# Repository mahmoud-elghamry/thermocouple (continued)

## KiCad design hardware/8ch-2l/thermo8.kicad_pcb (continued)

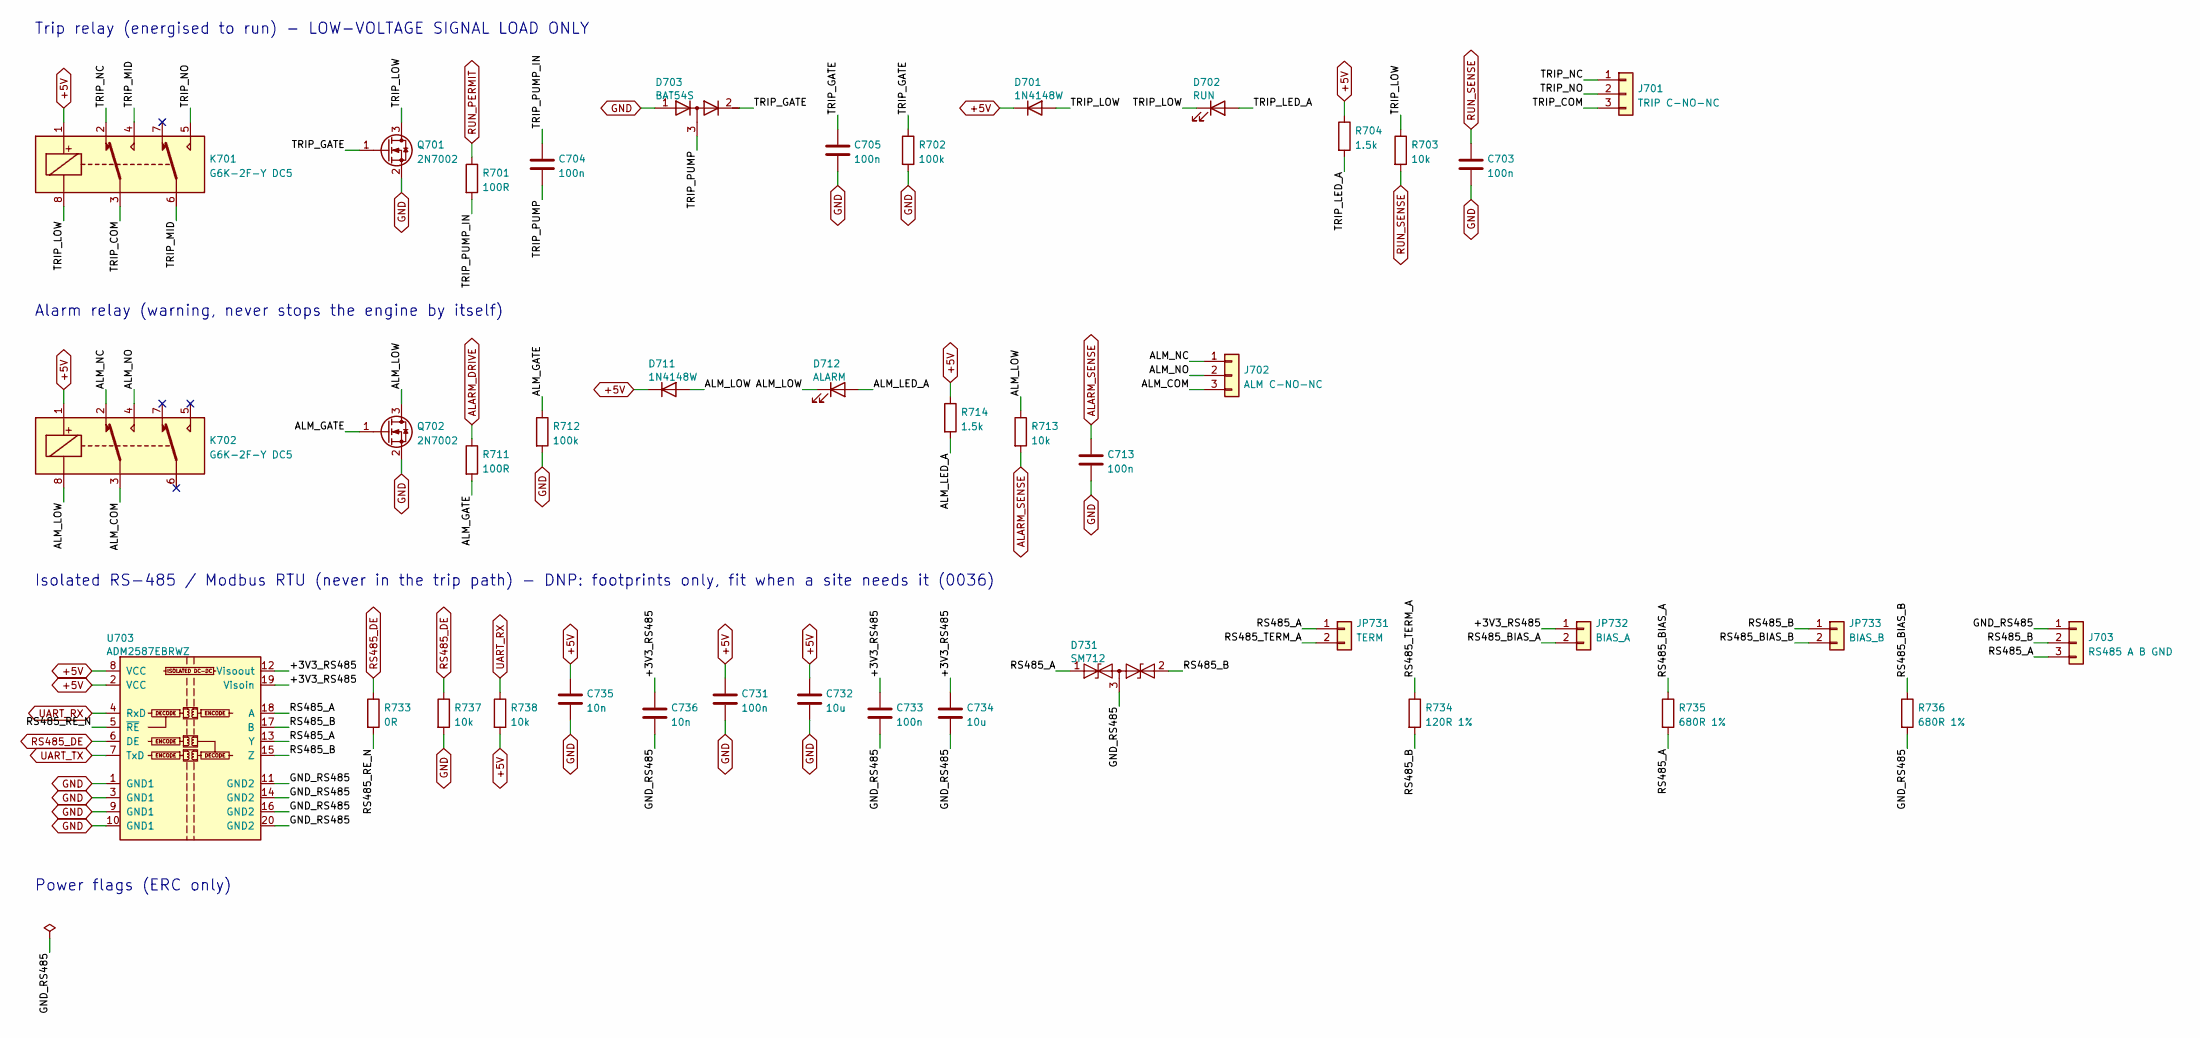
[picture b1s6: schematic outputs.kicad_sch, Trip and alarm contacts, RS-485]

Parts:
C703, C704, C705, C713, C731, C733: 100n; C_0805_2012Metric; MPN CC0805KRX7R9BB104; LCSC C49678
C732, C734: 10u; C_0805_2012Metric; MPN CL21B106KOQNNNE; LCSC C95841
C735, C736: 10n; C_0805_2012Metric; MPN CL21B103KBANNNC; LCSC C1710
D701, D711: 1N4148W; D_SOD-123; MPN 1N4148W-7-F; LCSC C83528
D702: RUN; LED_D3.0mm; MPN 3A4GUD; LCSC C52034646
D703: BAT54S; SOT-23; MPN BAT54S,215; LCSC C47546
D712: ALARM; LED_D3.0mm; MPN 204-10SURD/S530-A3-L; LCSC C99771
D731: SM712; SOT-23; MPN SM712.TCT; LCSC C12067
J701: TRIP C-NO-NC; TerminalBlock_Phoenix_MKDS-1,5-3_1x03_P5.00mm_Horizontal; MPN WJ128V-5.0-3P; LCSC C8270
J702: ALM C-NO-NC; TerminalBlock_Phoenix_MKDS-1,5-3_1x03_P5.00mm_Horizontal; MPN WJ128V-5.0-3P; LCSC C8270
J703: RS485 A B GND; TerminalBlock_Phoenix_MKDS-1,5-3_1x03_P5.00mm_Horizontal; MPN WJ128V-5.0-3P; LCSC C8270
JP731: TERM; PinHeader_1x02_P2.54mm_Vertical; MPN PZ254V-11-02P; LCSC C492401
JP732: BIAS_A; PinHeader_1x02_P2.54mm_Vertical; MPN PZ254V-11-02P; LCSC C492401
JP733: BIAS_B; PinHeader_1x02_P2.54mm_Vertical; MPN PZ254V-11-02P; LCSC C492401
K701, K702: G6K-2F-Y DC5; Relay_DPDT_Omron_G6K-2F-Y; MPN G6K-2F-Y DC5; LCSC C2982926
Q701, Q702: 2N7002; SOT-23; MPN 2N7002; LCSC C8545
R701, R711: 100R; R_0805_2012Metric; MPN 0805W8F1000T5E; LCSC C17408
R702, R712: 100k; R_0805_2012Metric; MPN 0805W8F1003T5E; LCSC C149504
R703, R713, R737, R738: 10k; R_0805_2012Metric; MPN 0805W8F1002T5E; LCSC C17414
R704, R714: 1.5k; R_0805_2012Metric; MPN 0805W8F1501T5E; LCSC C4310
R733: 0R; R_0805_2012Metric; MPN 0805W8F0000T5E; LCSC C17477
R734: 120R 1%; R_0805_2012Metric; MPN 0805W8F1200T5E; LCSC C17437
R735, R736: 680R 1%; R_0805_2012Metric; MPN 0805W8F6800T5E; LCSC C17798
U703: ADM2587EBRWZ; SOIC-20W_7.5x12.8mm_P1.27mm; MPN ADM2587EBRWZ-REEL7; LCSC C12081

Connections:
+5V: C731.1, C732.1, C735.1, D701.1 (K), D711.1 (K), K701.1, K702.1, R704.1, R714.1, R738.2, U703.2 (VCC), U703.8 (VCC); also elsewhere on the board
/OUTPUTS/+3V3_RS485: C733.1, C734.1, C736.1, JP732.1, U703.12 (Visoout), U703.19 (Visoin)
/OUTPUTS/ALM_COM: J702.3, K702.3
/OUTPUTS/ALM_GATE: Q702.1 (G), R711.2, R712.1
/OUTPUTS/ALM_LED_A: D712.2 (A), R714.2
/OUTPUTS/ALM_LOW: D711.2 (A), D712.1 (K), K702.8, Q702.3 (D), R713.1
/OUTPUTS/ALM_NC: J702.1, K702.2
/OUTPUTS/ALM_NO: J702.2, K702.4
/OUTPUTS/GND_RS485: C733.2, C734.2, C736.2, D731.3 (common), J703.1, R736.2, U703.11 (GND2), U703.14 (GND2), U703.16 (GND2), U703.20 (GND2)
/OUTPUTS/RS485_A: D731.1 (A1), J703.3, JP731.1, R735.2, U703.13 (Y), U703.18 (A)
/OUTPUTS/RS485_B: D731.2 (A2), J703.2, JP733.1, R734.2, U703.15 (Z), U703.17 (B)
/OUTPUTS/RS485_BIAS_A: JP732.2, R735.1
/OUTPUTS/RS485_BIAS_B: JP733.2, R736.1
/OUTPUTS/RS485_RE_N: R733.2, U703.5 (~RE)
/OUTPUTS/RS485_TERM_A: JP731.2, R734.1
/OUTPUTS/TRIP_COM: J701.3, K701.3
/OUTPUTS/TRIP_GATE: C705.1, D703.2 (K), Q701.1 (G), R702.1
/OUTPUTS/TRIP_LED_A: D702.2 (A), R704.2
/OUTPUTS/TRIP_LOW: D701.2 (A), D702.1 (K), K701.8, Q701.3 (D), R703.1
/OUTPUTS/TRIP_MID: K701.4, K701.6
/OUTPUTS/TRIP_NC: J701.1, K701.2
/OUTPUTS/TRIP_NO: J701.2, K701.5
/OUTPUTS/TRIP_PUMP: C704.2, D703.3 (common)
/OUTPUTS/TRIP_PUMP_IN: C704.1, R701.2
ALARM_DRIVE: R711.1; also elsewhere on the board
ALARM_SENSE: C713.1, R713.2; also elsewhere on the board
GND: C703.2, C705.2, C713.2, C731.2, C732.2, C735.2, D703.1 (A), Q701.2 (S), Q702.2 (S), R702.2, R712.2, R737.2, U703.1 (GND1), U703.3 (GND1), U703.9 (GND1), U703.10 (GND1); also elsewhere on the board
RS485_DE: R733.1, R737.1, U703.6 (DE); also elsewhere on the board
RUN_PERMIT: R701.1; also elsewhere on the board
RUN_SENSE: C703.1, R703.2; also elsewhere on the board
UART_RX: R738.1, U703.4 (RxD); also elsewhere on the board
UART_TX: U703.7 (TxD); also elsewhere on the board

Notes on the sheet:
Trip relay (energised to run) - LOW-VOLTAGE SIGNAL LOAD ONLY
Alarm relay (warning, never stops the engine by itself)
Isolated RS-485 / Modbus RTU (never in the trip path) - DNP: footprints only, fit when a site needs it (0036)
Power flags (ERC only)

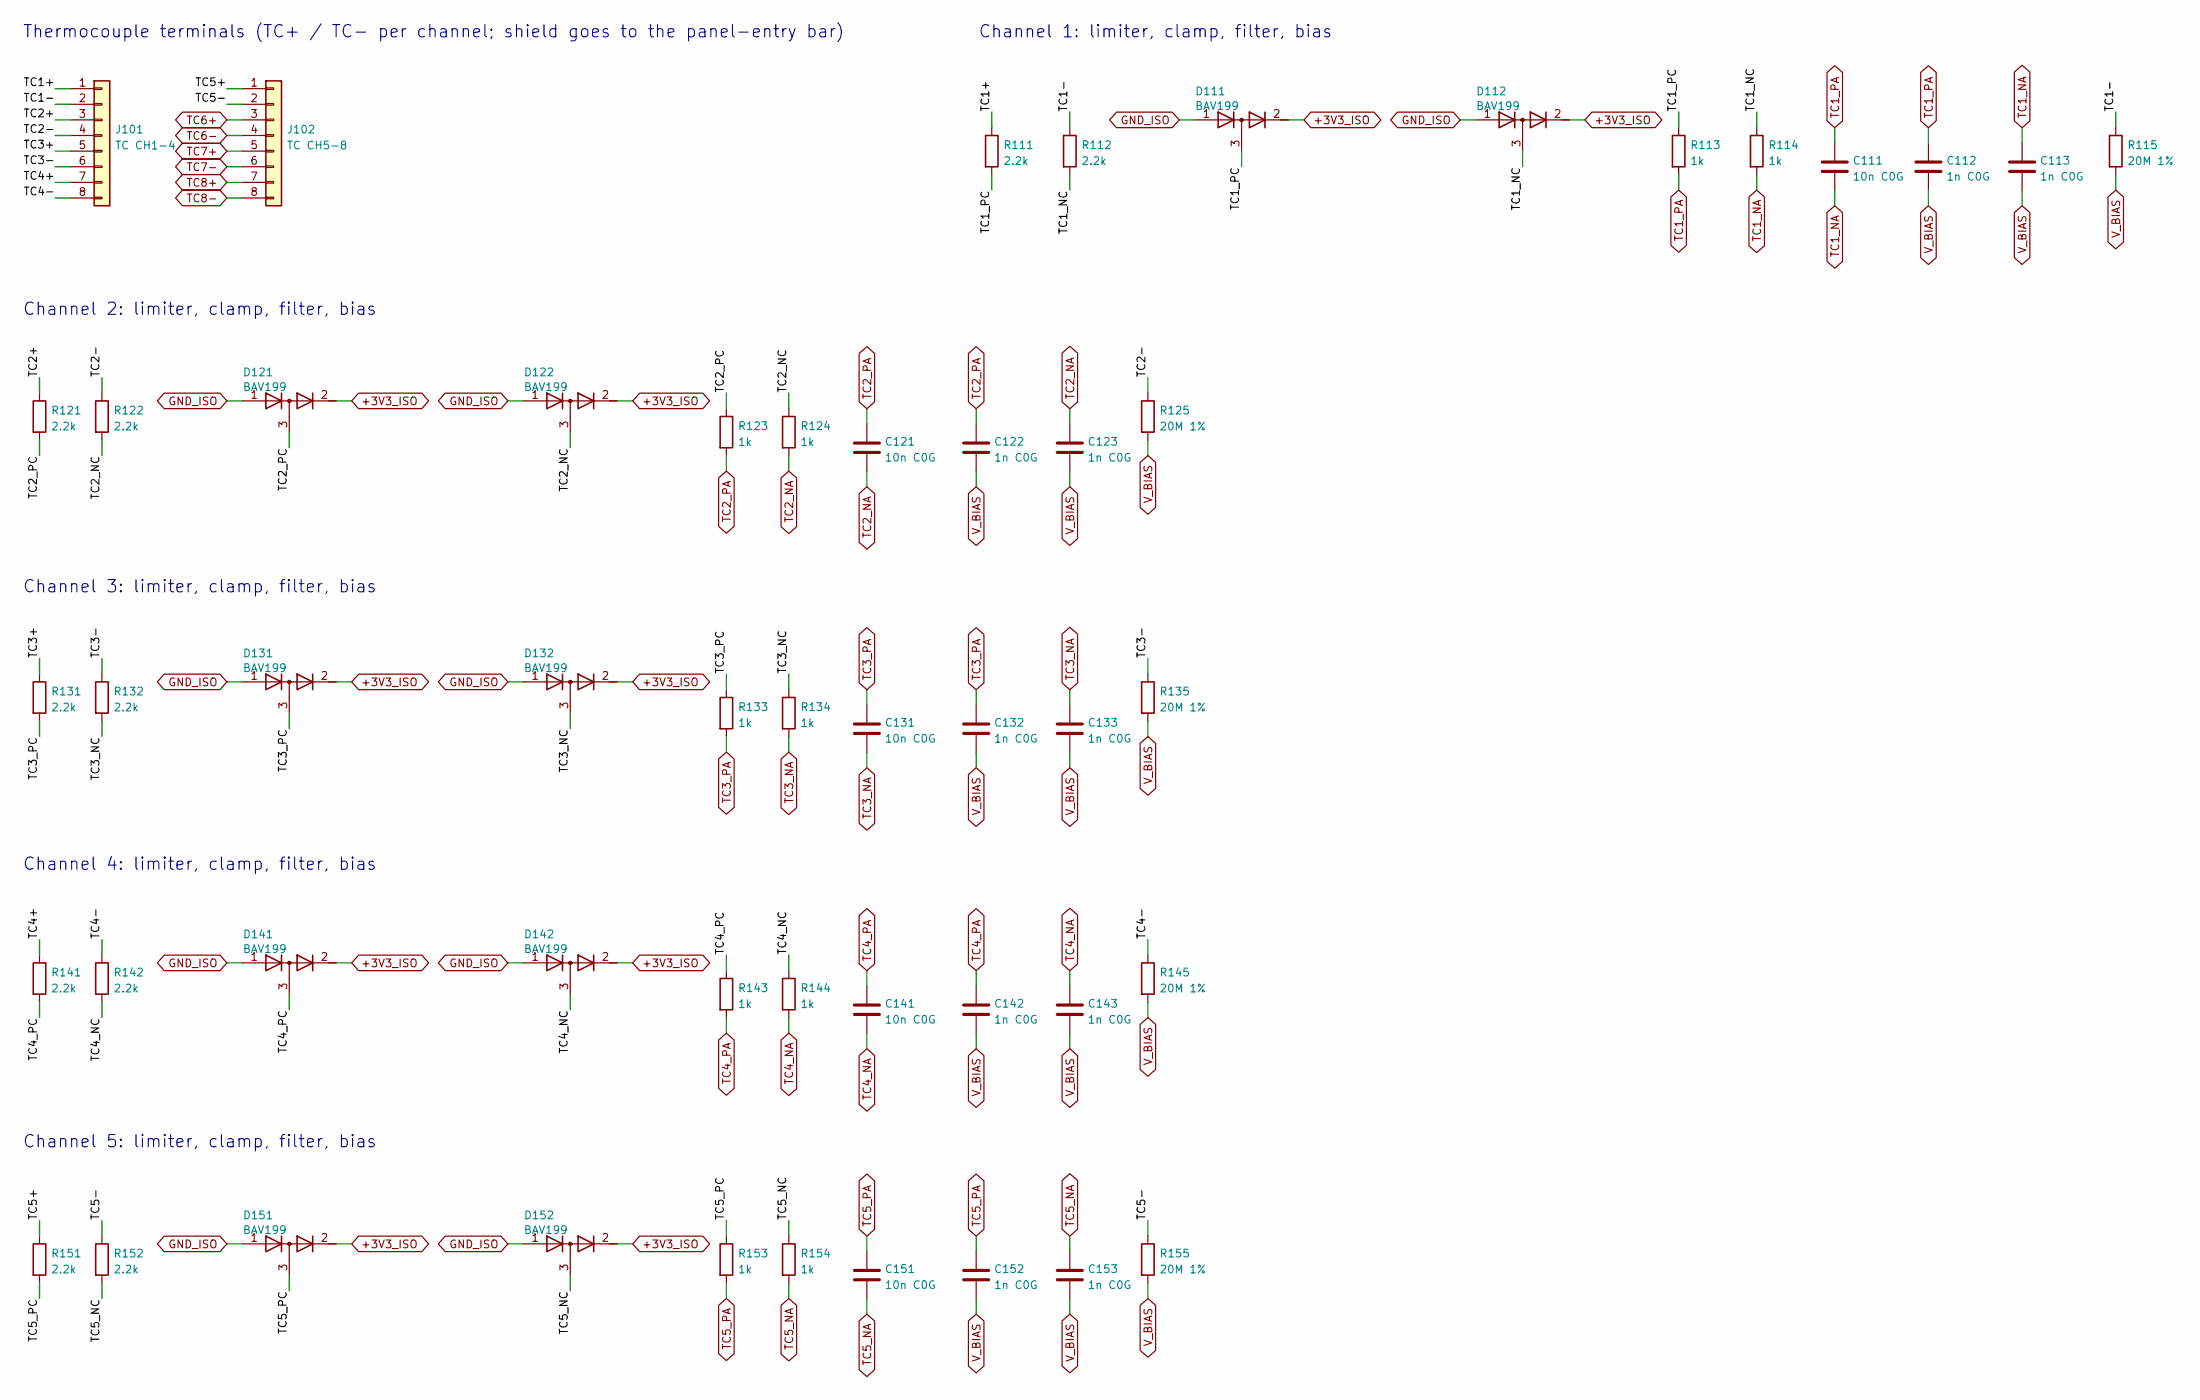
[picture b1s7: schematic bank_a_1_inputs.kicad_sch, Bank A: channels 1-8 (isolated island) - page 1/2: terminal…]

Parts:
C111, C121, C131, C141, C151: 10n C0G; C_0805_2012Metric; MPN GRM2195C1H103JA01D; LCSC C97905
C112, C113, C122, C123, C132, C133, C142, C143, C152, C153: 1n C0G; C_0805_2012Metric; MPN CL21C102JBCNNNC; LCSC C1791
D111, D112, D121, D122, D131, D132, D141, D142, D151, D152: BAV199; SOT-23; MPN BAV199,215; LCSC C40919
J101: TC CH1-4; PhoenixContact_MC_1,5_8-G-3.81_1x08_P3.81mm_Horizontal; MPN WJ15EDGRC-3.81-8P; LCSC C14235
J102: TC CH5-8; PhoenixContact_MC_1,5_8-G-3.81_1x08_P3.81mm_Horizontal; MPN WJ15EDGRC-3.81-8P; LCSC C14235
R111, R112, R121, R122, R131, R132, R141, R142, R151, R152: 2.2k; R_0805_2012Metric; MPN 0805W8F2201T5E; LCSC C17520
R113, R114, R123, R124, R133, R134, R143, R144, R153, R154: 1k; R_0805_2012Metric; MPN 0805W8F1001T5E; LCSC C17513
R115, R125, R135, R145, R155: 20M 1%; R_1206_3216Metric; MPN FRG1206F2005TS; LCSC C3000606

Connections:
+3V3_ISO: D111.2 (K), D112.2 (K), D121.2 (K), D122.2 (K), D131.2 (K), D132.2 (K), D141.2 (K), D142.2 (K), D151.2 (K), D152.2 (K); also elsewhere on the board
/BANK_A_1/TC1+: J101.1, R111.1
/BANK_A_1/TC1-: J101.2, R112.1, R115.1
/BANK_A_1/TC1_NC: D112.3 (common), R112.2, R114.1
/BANK_A_1/TC1_PC: D111.3 (common), R111.2, R113.1
/BANK_A_1/TC2+: J101.3, R121.1
/BANK_A_1/TC2-: J101.4, R122.1, R125.1
/BANK_A_1/TC2_NC: D122.3 (common), R122.2, R124.1
/BANK_A_1/TC2_PC: D121.3 (common), R121.2, R123.1
/BANK_A_1/TC3+: J101.5, R131.1
/BANK_A_1/TC3-: J101.6, R132.1, R135.1
/BANK_A_1/TC3_NC: D132.3 (common), R132.2, R134.1
/BANK_A_1/TC3_PC: D131.3 (common), R131.2, R133.1
/BANK_A_1/TC4+: J101.7, R141.1
/BANK_A_1/TC4-: J101.8, R142.1, R145.1
/BANK_A_1/TC4_NC: D142.3 (common), R142.2, R144.1
/BANK_A_1/TC4_PC: D141.3 (common), R141.2, R143.1
/BANK_A_1/TC5+: J102.1, R151.1
/BANK_A_1/TC5-: J102.2, R152.1, R155.1
/BANK_A_1/TC5_NC: D152.3 (common), R152.2, R154.1
/BANK_A_1/TC5_PC: D151.3 (common), R151.2, R153.1
GND_ISO: D111.1 (A), D112.1 (A), D121.1 (A), D122.1 (A), D131.1 (A), D132.1 (A), D141.1 (A), D142.1 (A), D151.1 (A), D152.1 (A); also elsewhere on the board
TC1_NA: C111.2, C113.1, R114.2; also elsewhere on the board
TC1_PA: C111.1, C112.1, R113.2; also elsewhere on the board
TC2_NA: C121.2, C123.1, R124.2; also elsewhere on the board
TC2_PA: C121.1, C122.1, R123.2; also elsewhere on the board
TC3_NA: C131.2, C133.1, R134.2; also elsewhere on the board
TC3_PA: C131.1, C132.1, R133.2; also elsewhere on the board
TC4_NA: C141.2, C143.1, R144.2; also elsewhere on the board
TC4_PA: C141.1, C142.1, R143.2; also elsewhere on the board
TC5_NA: C151.2, C153.1, R154.2; also elsewhere on the board
TC5_PA: C151.1, C152.1, R153.2; also elsewhere on the board
TC6+: J102.3; also elsewhere on the board
TC6-: J102.4; also elsewhere on the board
TC7+: J102.5; also elsewhere on the board
TC7-: J102.6; also elsewhere on the board
TC8+: J102.7; also elsewhere on the board
TC8-: J102.8; also elsewhere on the board
V_BIAS: C112.2, C113.2, C122.2, C123.2, C132.2, C133.2, C142.2, C143.2, C152.2, C153.2, R115.2, R125.2, R135.2, R145.2, R155.2; also elsewhere on the board

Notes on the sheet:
Thermocouple terminals (TC+ / TC- per channel; shield goes to the panel-entry bar)
Channel 1: limiter, clamp, filter, bias
Channel 2: limiter, clamp, filter, bias
Channel 3: limiter, clamp, filter, bias
Channel 4: limiter, clamp, filter, bias
Channel 5: limiter, clamp, filter, bias

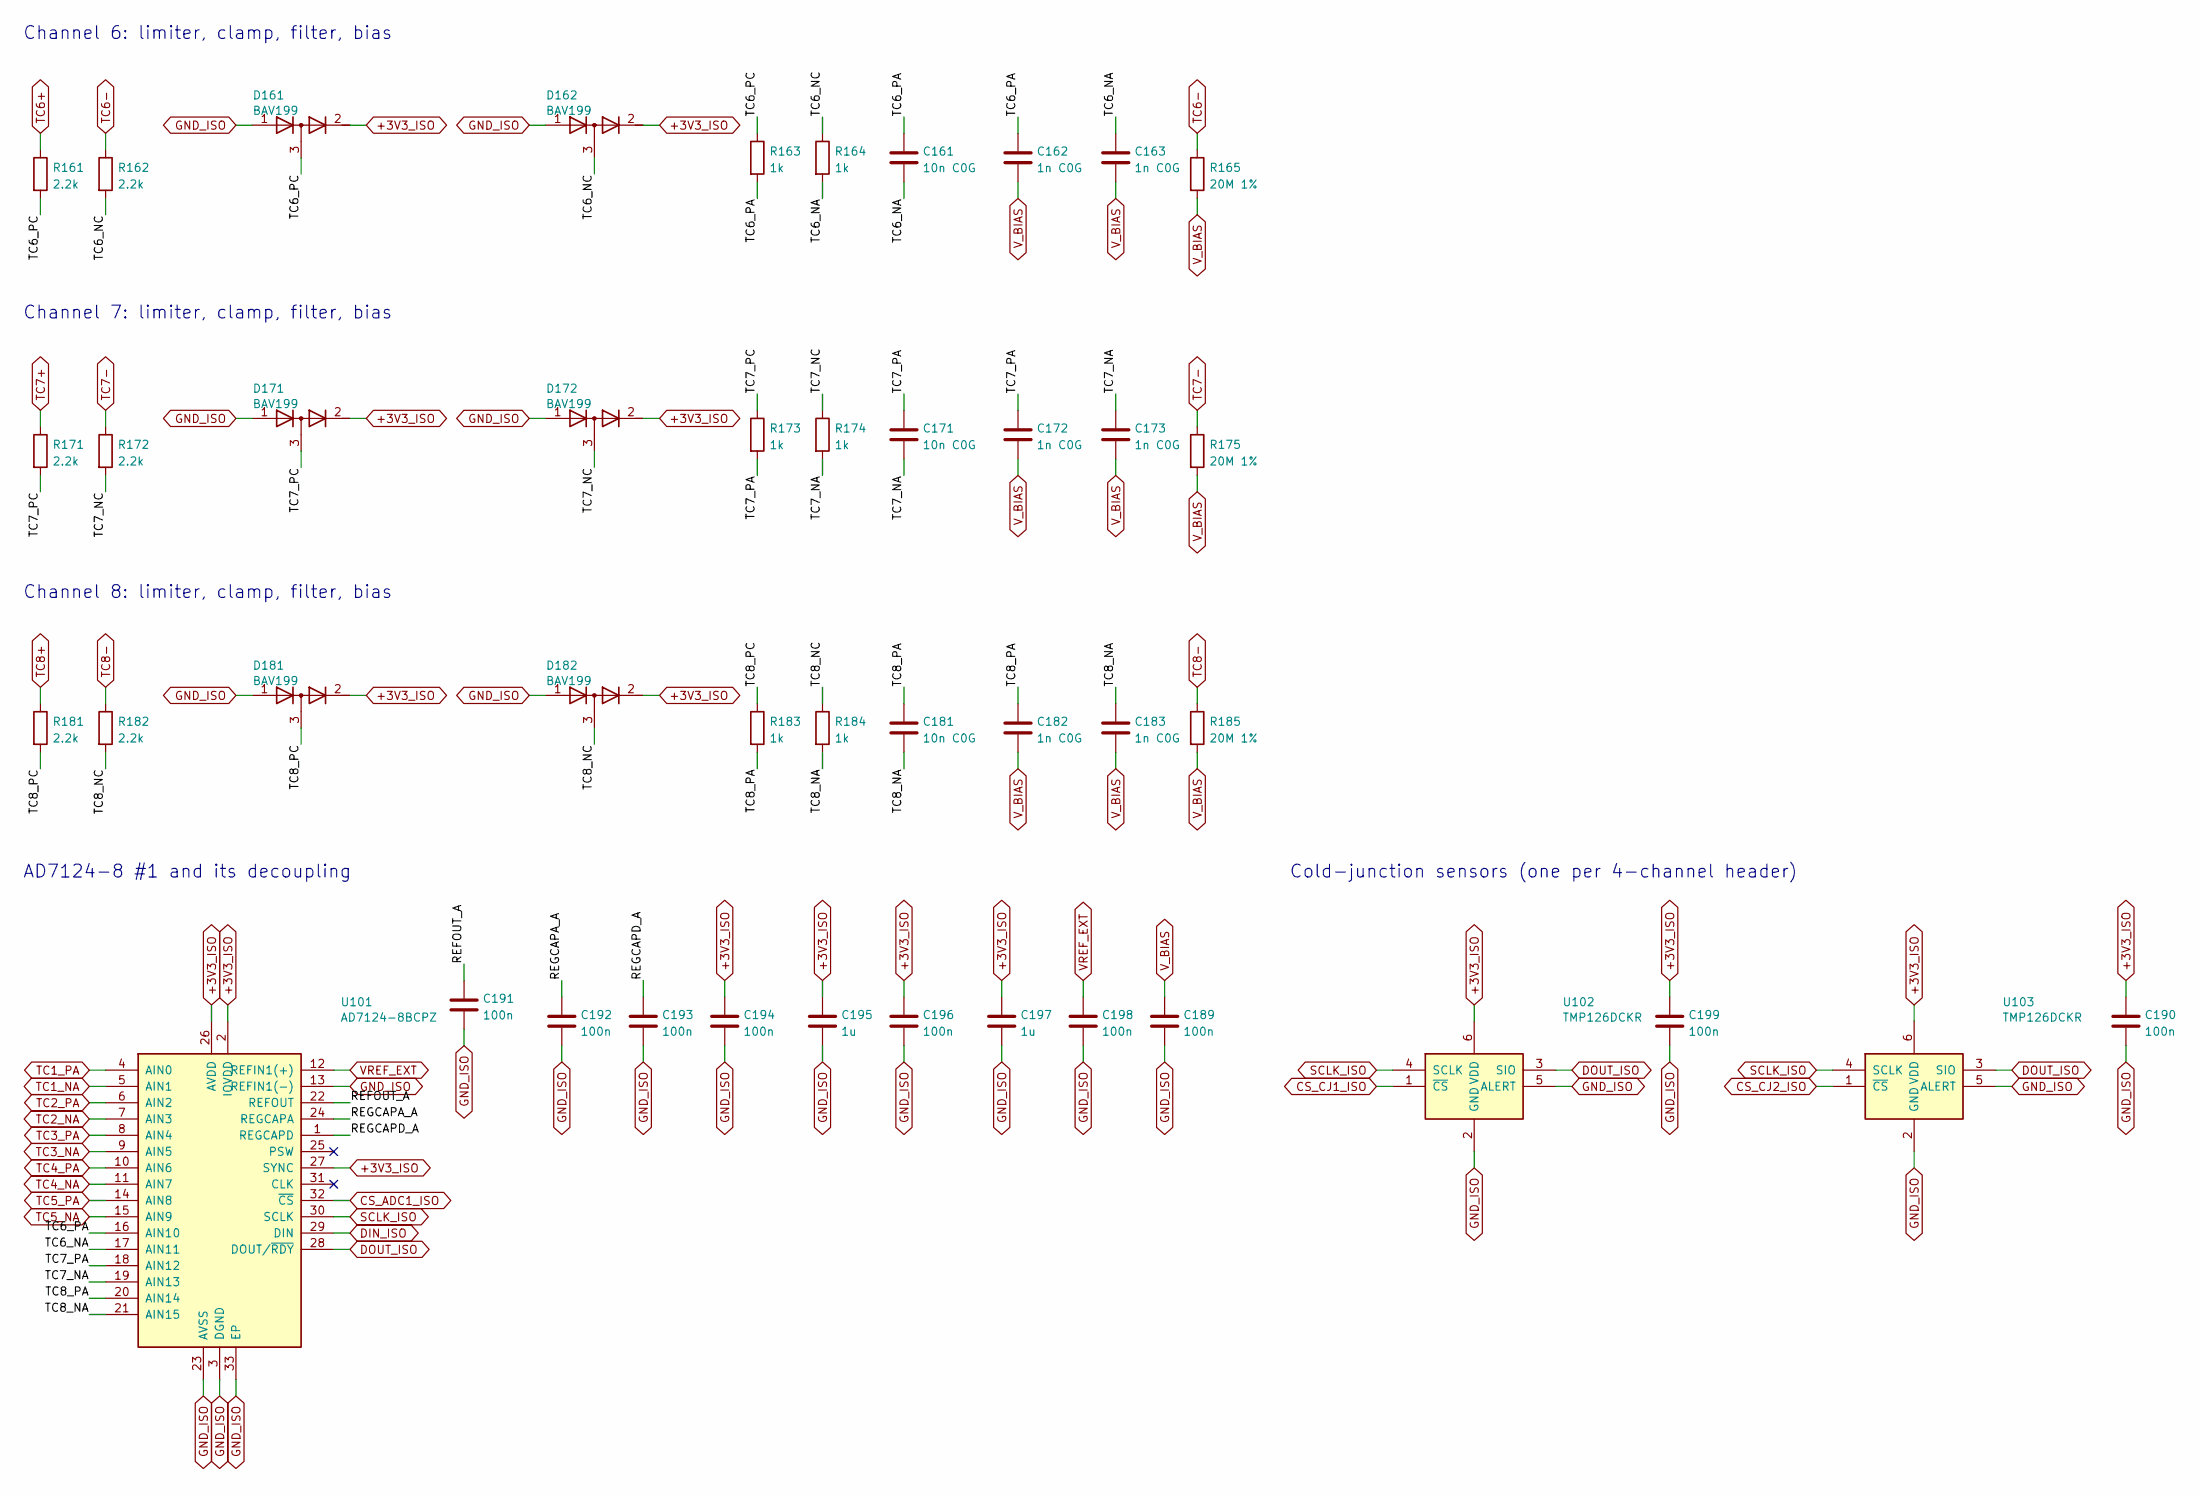
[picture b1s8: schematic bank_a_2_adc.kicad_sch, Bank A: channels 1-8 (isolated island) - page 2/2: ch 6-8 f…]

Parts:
C161, C171, C181: 10n C0G; C_0805_2012Metric; MPN GRM2195C1H103JA01D; LCSC C97905
C162, C163, C172, C173, C182, C183: 1n C0G; C_0805_2012Metric; MPN CL21C102JBCNNNC; LCSC C1791
C189, C190, C191, C192, C193, C194, C196, C198, C199: 100n; C_0805_2012Metric; MPN CC0805KRX7R9BB104; LCSC C49678
C195, C197: 1u; C_0805_2012Metric; MPN CL21B105KBFNNNE; LCSC C28323
D161, D162, D171, D172, D181, D182: BAV199; SOT-23; MPN BAV199,215; LCSC C40919
R161, R162, R171, R172, R181, R182: 2.2k; R_0805_2012Metric; MPN 0805W8F2201T5E; LCSC C17520
R163, R164, R173, R174, R183, R184: 1k; R_0805_2012Metric; MPN 0805W8F1001T5E; LCSC C17513
R165, R175, R185: 20M 1%; R_1206_3216Metric; MPN FRG1206F2005TS; LCSC C3000606
U101: AD7124-8BCPZ; LFCSP-32-1EP_5x5mm_P0.5mm_EP3.6x3.6mm; MPN AD7124-8BCPZ; LCSC C97314
U102, U103: TMP126DCKR; SOT-363_SC-70-6; MPN TMP126DCKR; LCSC C5219998

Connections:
+3V3_ISO: C190.1, C194.1, C195.1, C196.1, C197.1, C199.1, D161.2 (K), D162.2 (K), D171.2 (K), D172.2 (K), D181.2 (K), D182.2 (K), U101.2 (IOVDD), U101.26 (AVDD), U101.27 (SYNC), U102.6 (VDD), U103.6 (VDD); also elsewhere on the board
/BANK_A_2/REFOUT_A: C191.1, U101.22 (REFOUT)
/BANK_A_2/REGCAPA_A: C192.1, U101.24 (REGCAPA)
/BANK_A_2/REGCAPD_A: C193.1, U101.1 (REGCAPD)
/BANK_A_2/TC6_NA: C161.2, C163.1, R164.2, U101.17 (AIN11)
/BANK_A_2/TC6_NC: D162.3 (common), R162.2, R164.1
/BANK_A_2/TC6_PA: C161.1, C162.1, R163.2, U101.16 (AIN10)
/BANK_A_2/TC6_PC: D161.3 (common), R161.2, R163.1
/BANK_A_2/TC7_NA: C171.2, C173.1, R174.2, U101.19 (AIN13)
/BANK_A_2/TC7_NC: D172.3 (common), R172.2, R174.1
/BANK_A_2/TC7_PA: C171.1, C172.1, R173.2, U101.18 (AIN12)
/BANK_A_2/TC7_PC: D171.3 (common), R171.2, R173.1
/BANK_A_2/TC8_NA: C181.2, C183.1, R184.2, U101.21 (AIN15)
/BANK_A_2/TC8_NC: D182.3 (common), R182.2, R184.1
/BANK_A_2/TC8_PA: C181.1, C182.1, R183.2, U101.20 (AIN14)
/BANK_A_2/TC8_PC: D181.3 (common), R181.2, R183.1
CS_ADC1_ISO: U101.32 (~CS); also elsewhere on the board
CS_CJ1_ISO: U102.1 (~CS); also elsewhere on the board
CS_CJ2_ISO: U103.1 (~CS); also elsewhere on the board
DIN_ISO: U101.29 (DIN); also elsewhere on the board
DOUT_ISO: U101.28 (DOUT/~RDY), U102.3 (SIO), U103.3 (SIO); also elsewhere on the board
GND_ISO: C189.2, C190.2, C191.2, C192.2, C193.2, C194.2, C195.2, C196.2, C197.2, C198.2, C199.2, D161.1 (A), D162.1 (A), D171.1 (A), D172.1 (A), D181.1 (A), D182.1 (A), U101.3 (DGND), U101.13 (REFIN1(-)), U101.23 (AVSS), U101.33 (EP), U102.2 (GND), U102.5 (ALERT), U103.2 (GND), U103.5 (ALERT); also elsewhere on the board
SCLK_ISO: U101.30 (SCLK), U102.4 (SCLK), U103.4 (SCLK); also elsewhere on the board
TC1_NA: U101.5 (AIN1); also elsewhere on the board
TC1_PA: U101.4 (AIN0); also elsewhere on the board
TC2_NA: U101.7 (AIN3); also elsewhere on the board
TC2_PA: U101.6 (AIN2); also elsewhere on the board
TC3_NA: U101.9 (AIN5); also elsewhere on the board
TC3_PA: U101.8 (AIN4); also elsewhere on the board
TC4_NA: U101.11 (AIN7); also elsewhere on the board
TC4_PA: U101.10 (AIN6); also elsewhere on the board
TC5_NA: U101.15 (AIN9); also elsewhere on the board
TC5_PA: U101.14 (AIN8); also elsewhere on the board
TC6+: R161.1; also elsewhere on the board
TC6-: R162.1, R165.1; also elsewhere on the board
TC7+: R171.1; also elsewhere on the board
TC7-: R172.1, R175.1; also elsewhere on the board
TC8+: R181.1; also elsewhere on the board
TC8-: R182.1, R185.1; also elsewhere on the board
VREF_EXT: C198.1, U101.12 (REFIN1(+)); also elsewhere on the board
V_BIAS: C162.2, C163.2, C172.2, C173.2, C182.2, C183.2, C189.1, R165.2, R175.2, R185.2; also elsewhere on the board

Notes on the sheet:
Channel 6: limiter, clamp, filter, bias
Channel 7: limiter, clamp, filter, bias
Channel 8: limiter, clamp, filter, bias
AD7124-8 #1 and its decoupling
Cold-junction sensors (one per 4-channel header)

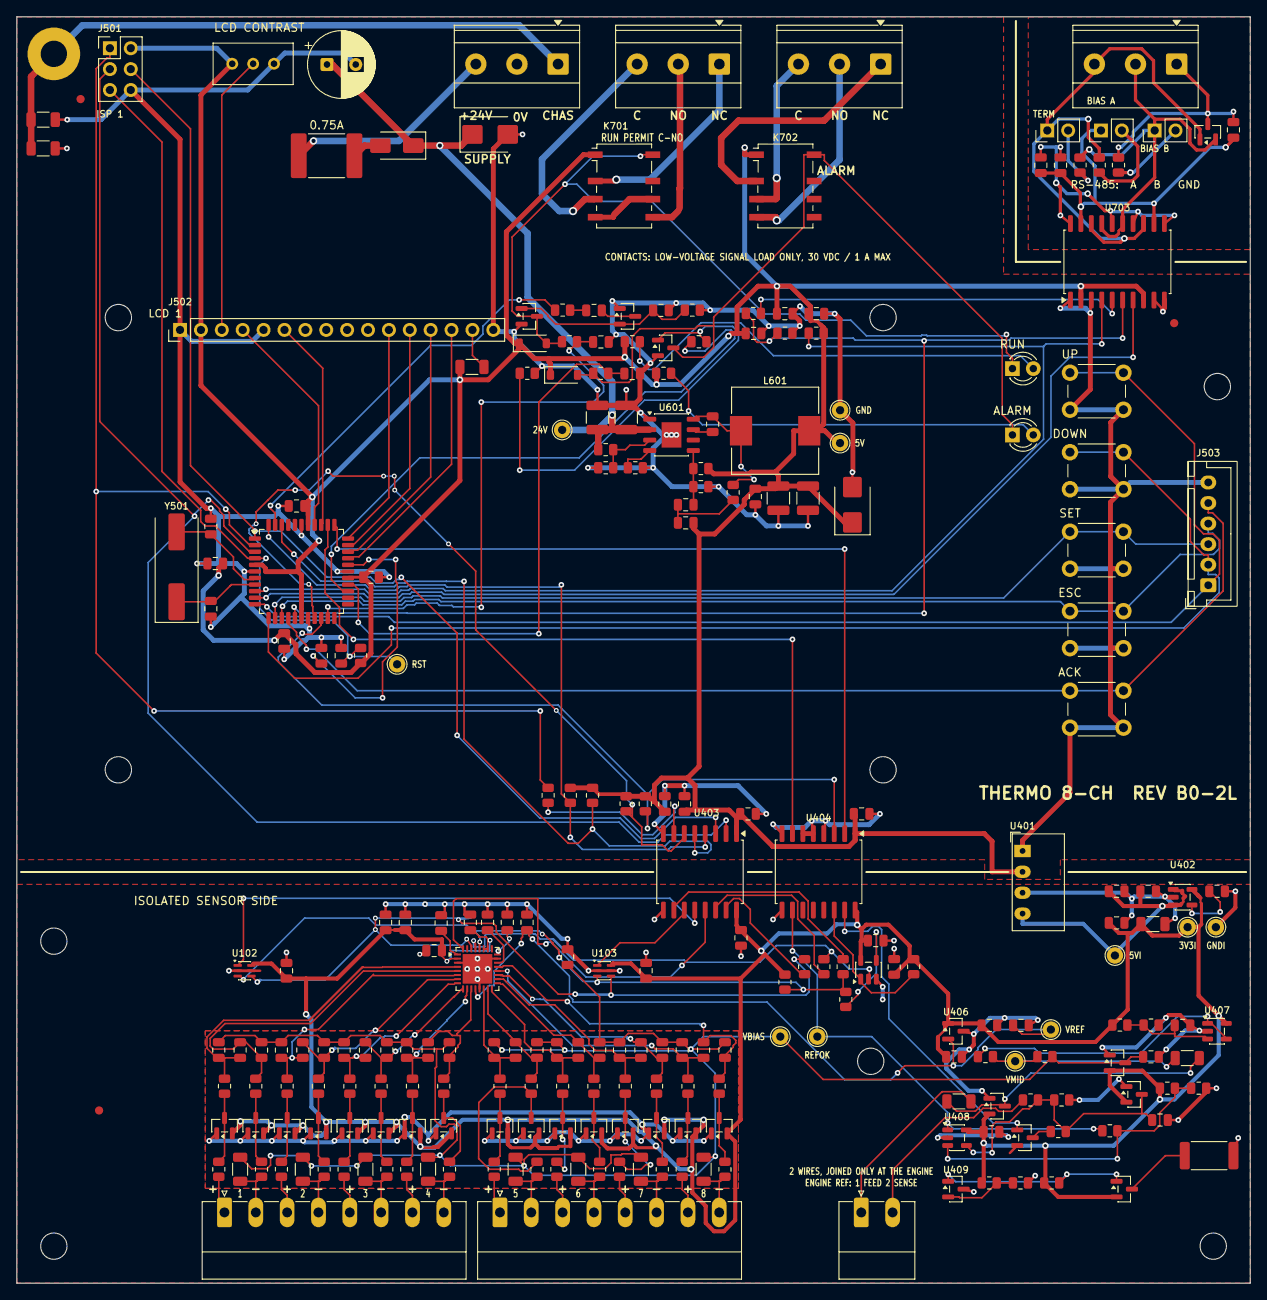
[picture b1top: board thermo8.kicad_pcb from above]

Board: 2 copper layers, 150.0 x 154.0 mm, 267 parts (0 on the bottom side), 151 nets.

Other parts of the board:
C601: 22u 100V; CP_Radial_D8.0mm_P3.50mm
C602, C603: 4.7u 100V; C_1210_3225Metric
C604: 2.2n C0G; C_0805_2012Metric
C605, C606: 22u 25V; C_1210_3225Metric
C607: 10u; C_0805_2012Metric
C608: 3.3n; C_0805_2012Metric
C609: 220p C0G; C_0805_2012Metric
C610: 1n 2kV; C_1206_3216Metric
D601: SS310; D_SMA
D602: SMBJ60A; D_SMB
D603: SMBJ5.0A; D_SMB
F601: 0.75A 60V; Fuse_2920_7451Metric
FID1, FID2, FID3: Fiducial_1mm_Mask2mm
J601: 24V IN; TerminalBlock_Phoenix_MKDS-1,5-3_1x03_P5.00mm_Horizontal
L601: 33u 2.2A; L_10.4x10.4_H4.8
R601: 41.2k 1%; R_0805_2012Metric
R602: 158k 1%; R_0805_2012Metric
R603: 49.9k 1%; R_0805_2012Metric
R604: 150k 1%; R_0805_2012Metric
R605: 33.2k 1%; R_0805_2012Metric
R606: 10k 1%; R_0805_2012Metric
R607: 1M; R_1206_3216Metric
TP601: GND; TestPoint_THTPad_D2.0mm_Drill1.0mm
TP602: +5V; TestPoint_THTPad_D2.0mm_Drill1.0mm
TP603: +24V_PROT; TestPoint_THTPad_D2.0mm_Drill1.0mm
U601: LM5164DDAR; HSOP-8-1EP_3.9x4.9mm_P1.27mm_EP2.41x3.1mm

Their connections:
+5V: C605.1, C606.1, C607.1, C608.2, D603.1 (K), L601.2, R602.1, TP602.1 (Pin_1_1); also elsewhere on the board
/POWER/+24V_FUSED: D601.2 (A), F601.2
/POWER/+24V_PROT: C601.1, C602.1, C603.1, D601.1 (K), D602.1 (K), R605.1, TP603.1 (Pin_1_1), U601.2 (VIN)
/POWER/+24V_RAW: F601.1, J601.3
/POWER/BST_5V: C604.1, U601.7 (BST)
/POWER/FB_5V: C609.2, R602.2, R603.1, U601.5 (FB)
/POWER/RIPPLE_INJ: C608.1, C609.1, R604.2
/POWER/RON_SET: R601.1, U601.4 (RON)
/POWER/SW_5V: C604.2, L601.1, R604.1, U601.8 (SW)
/POWER/VIN_UVLO: R605.2, R606.1, U601.3 (EN/UVLO)
CHASSIS: C610.1, J601.1, R607.1; also elsewhere on the board
GND: C601.2, C602.2, C603.2, C605.2, C606.2, C607.2, C610.2, D602.2 (A), D603.2 (A), J601.2, R601.2, R603.2, R606.2, R607.2, TP601.1 (Pin_1_1), U601.1 (GND), U601.9 (EP); also elsewhere on the board

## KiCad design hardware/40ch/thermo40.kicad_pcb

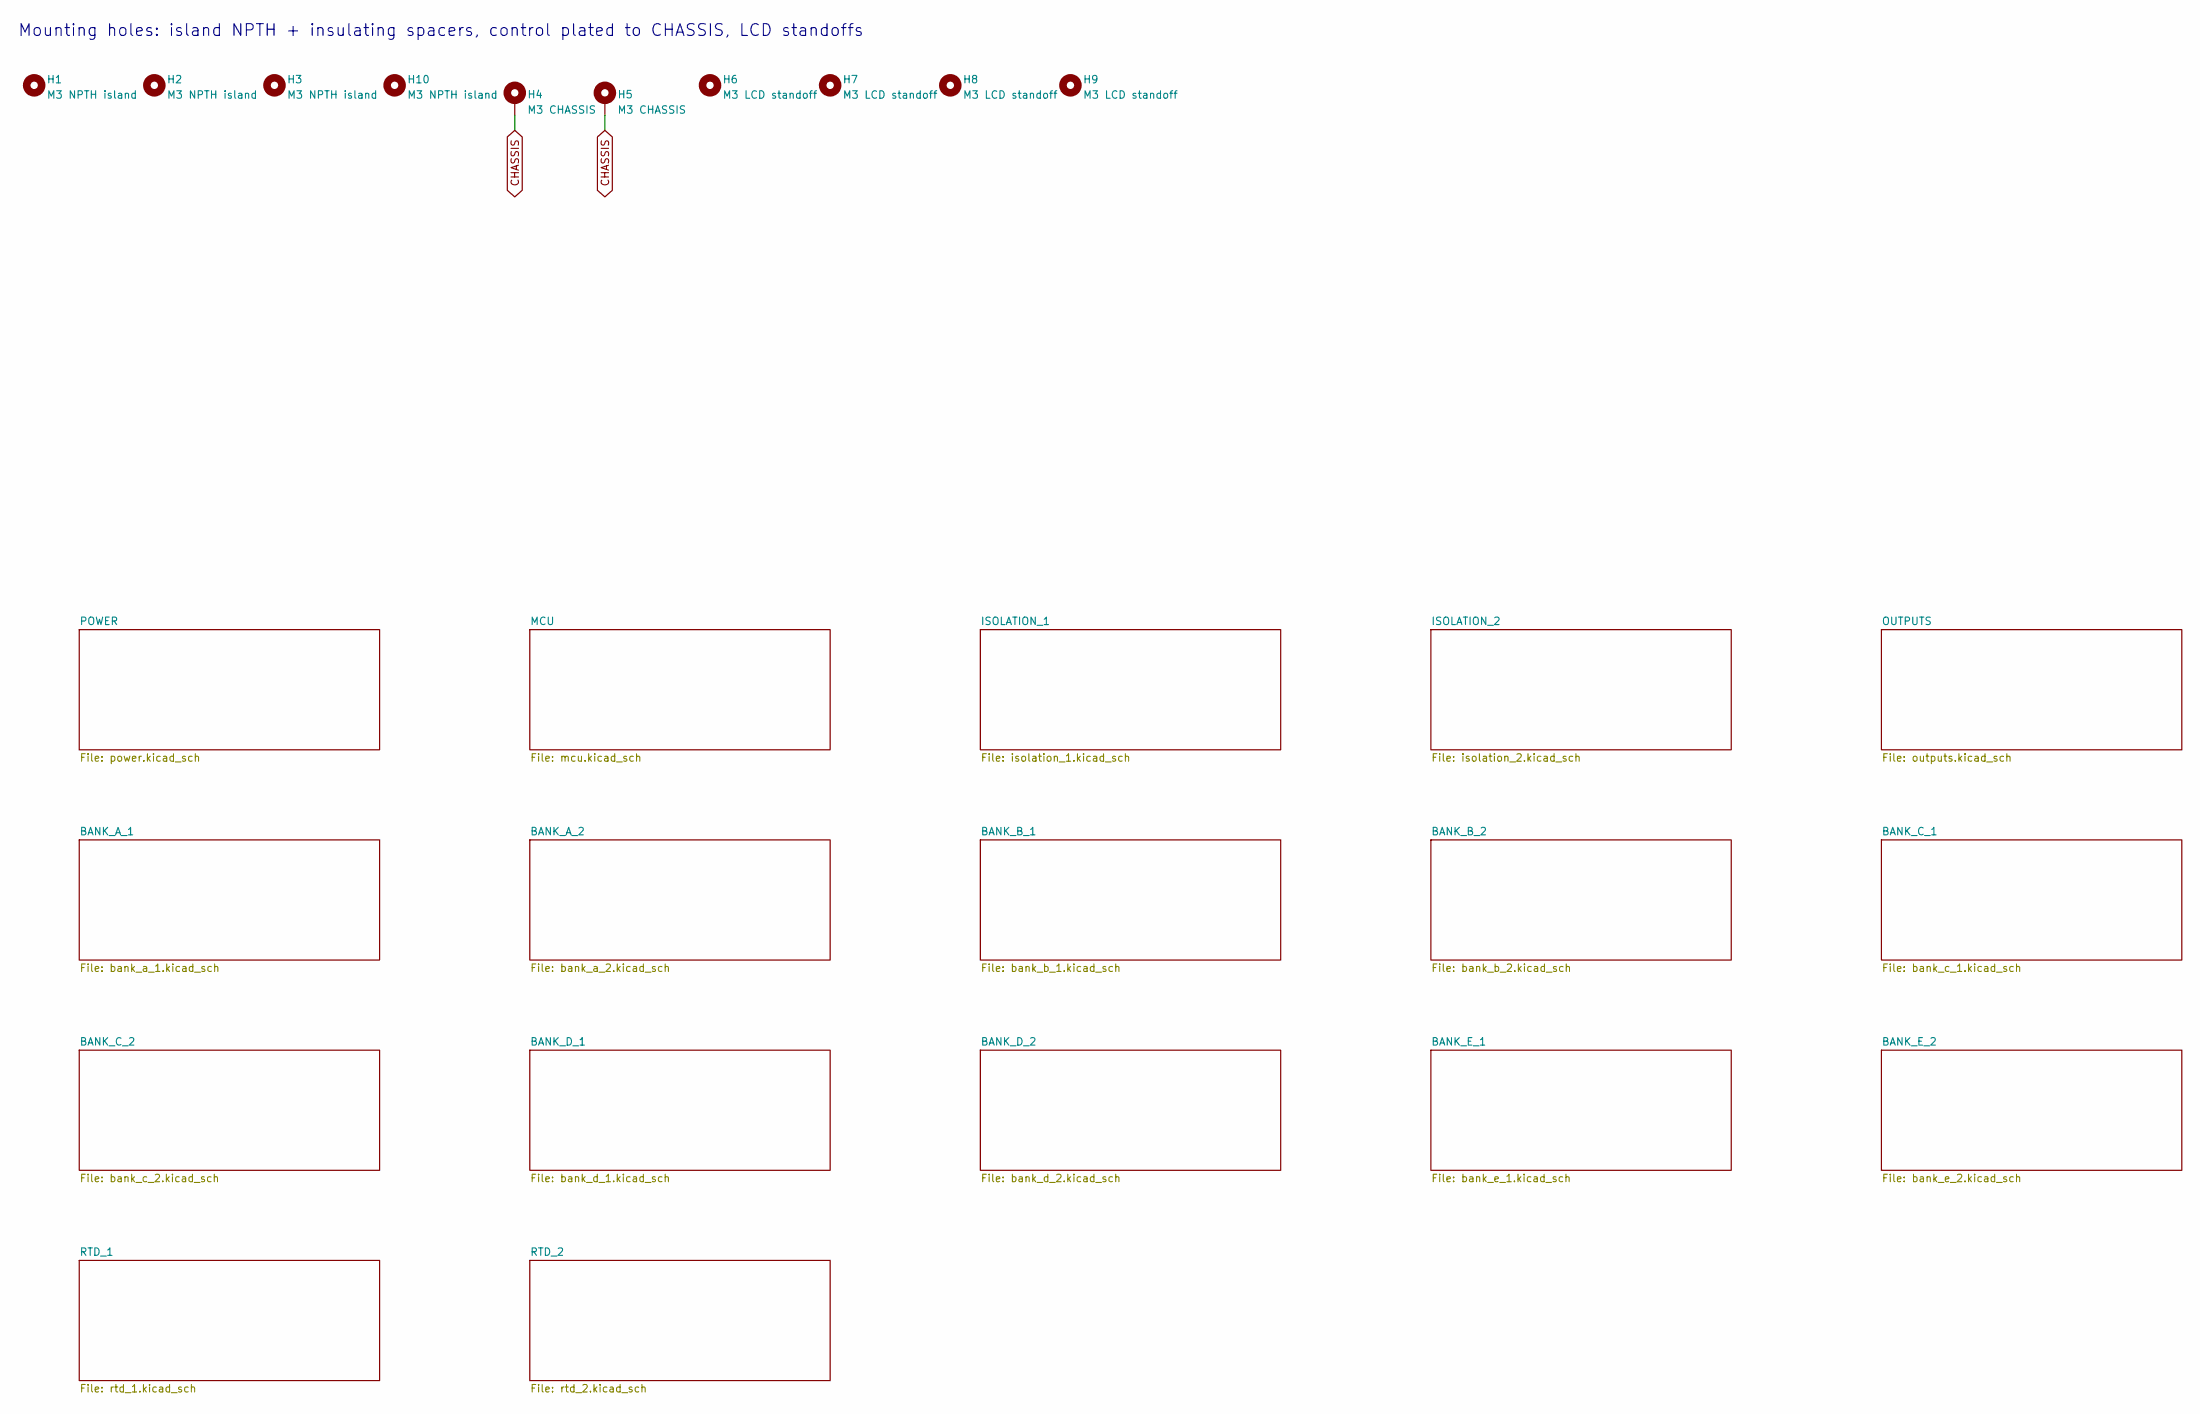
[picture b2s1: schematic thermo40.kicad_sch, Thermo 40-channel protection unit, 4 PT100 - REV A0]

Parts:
H1, H2, H3, H10: M3 NPTH island; MountingHole_3.2mm_M3
H4, H5: M3 CHASSIS; MountingHole_3.2mm_M3_Pad
H6, H7, H8, H9: M3 LCD standoff; MountingHole_3.2mm_M3

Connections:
CHASSIS: H4.1 (1_1), H5.1 (1_1); also elsewhere on the board

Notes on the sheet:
Mounting holes: island NPTH + insulating spacers, control plated to CHASSIS, LCD standoffs
